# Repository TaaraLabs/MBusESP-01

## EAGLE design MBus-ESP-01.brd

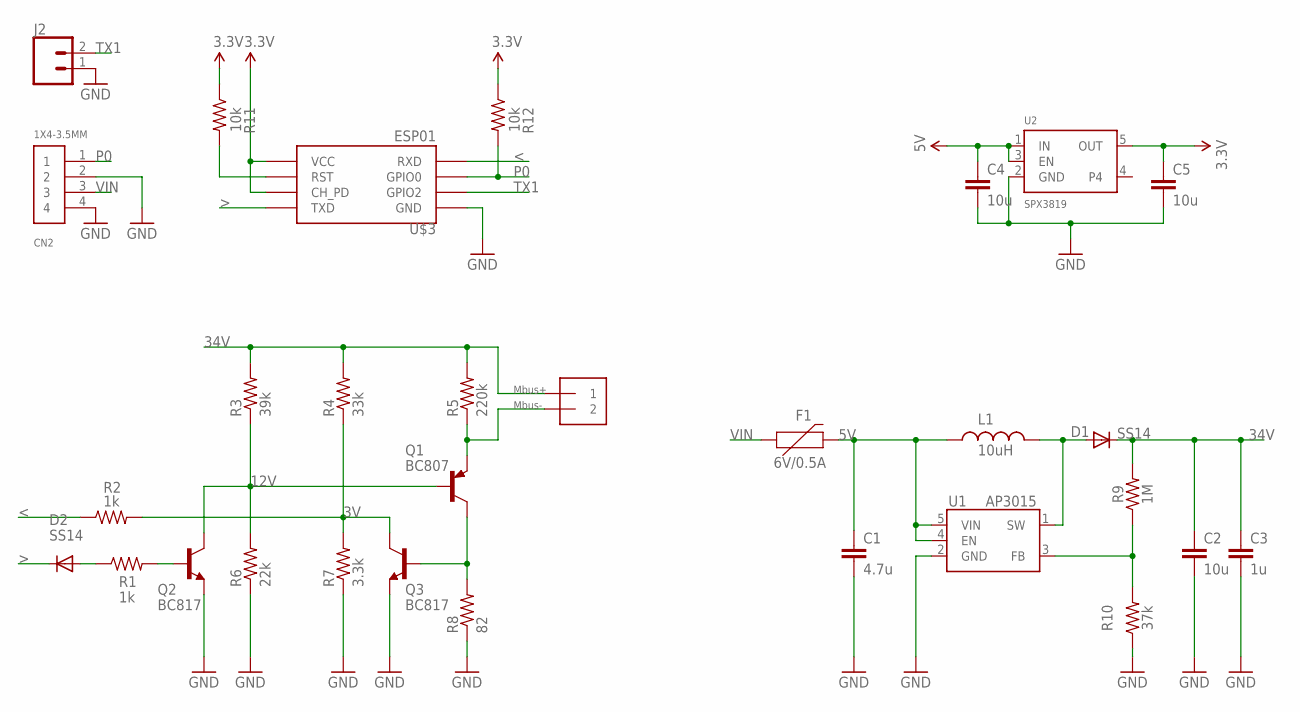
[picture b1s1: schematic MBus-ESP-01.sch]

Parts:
C1: 4.7u; 0805
C2: 10u; 1206
C3: 1u; 1206
C4, C5: 10u; 0603-CAP
CN2: 1X4-3.5MM; 1X04-3.5MM
D1, D2: SS14; SOD-123
F1: 6V/0.5A; 1206
J1: 1X2-3.5MM
J2: CONN_021X02_NO_SILK; 1X02_NO_SILK
L1: 10uH; B82462G
Q1: BC807; SOT23-BEC
Q2, Q3: BC817; SOT23-BEC
R1, R2: 1k; 0805
R3: 39k; 0805
R4: 33k; 0805
R5: 220k; 1206
R6: 22k; 0805
R7: 3.3k; 0805
R8: 82; 1206
R9: 1M; 0805
R10: 37k; 0805
R11, R12: 10k; 0805
U1: AP3015; SOT-23-5
U2: SPX3819; SOT23-5
U$3: ESP01

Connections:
3.3V: C5.1, R11.1, R12.1, U2.5 (OUT), U$3.CH_PD, U$3.VCC
3V: Q3.C, R2.2, R4.1, R7.2
5V: C1.1, C4.1, F1.2, L1.P$1 (1), U1.4 (EN), U1.5 (VIN), U2.1 (IN), U2.3 (EN)
12V: Q1.B, Q2.C, R3.1, R6.2
34V: C2.1, C3.1, D1.C, J1.1, R3.2, R4.2, R5.2, R9.2
<: R2.1, U$3.RX (RXD)
>: D2.C, U$3.TX (TXD)
GND: C1.2, C2.2, C3.2, C4.2, C5.2, CN2.2, CN2.4, J2.1, Q2.E, Q3.E, R6.1, R7.1, R8.1, R10.1, U1.2 (GND), U2.2 (GND), U$3.GND
MBUS-: J1.2, Q1.E, R5.1
unnamed: Q1.C, Q3.B, R8.2
unnamed: R9.1, R10.2, U1.3 (FB)
unnamed: D1.A, L1.P$2 (2), U1.1 (SW)
unnamed: D2.A, R1.1
unnamed: Q2.B, R1.2
P0: CN2.1, R12.2, U$3.GPIO0
RST: R11.2, U$3.RST
TX1: J2.2, U$3.GPIO2
VIN: CN2.3, F1.1

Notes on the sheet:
Mbus+
Mbus-

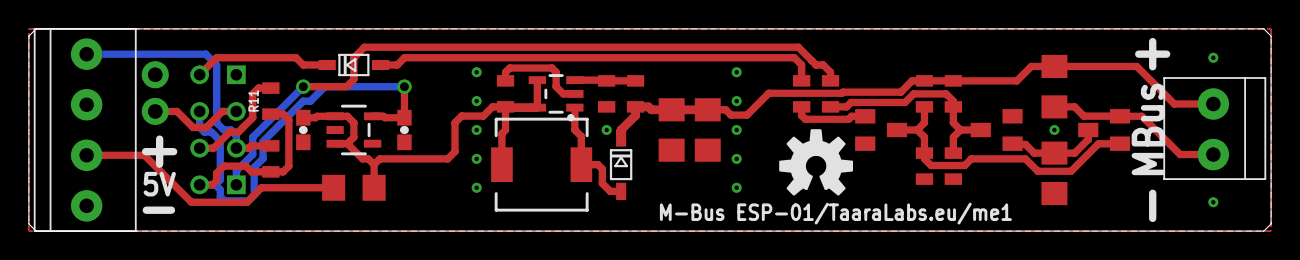
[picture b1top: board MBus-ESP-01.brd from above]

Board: 2 copper layers, 86.0 x 14.0 mm, 32 parts (1 on the bottom side), 18 nets.

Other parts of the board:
U$1, U$2: OSHW-LOGO-M

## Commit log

2019-03-23 Eagle files

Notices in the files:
parts and their libraries:
SparkFun: Licensing: CC v3.0 Share-Alike You are welcome to use this library for commercial purposes.
SparkFun-Capacitors: Licensing: Creative Commons ShareAlike 4.0 International - https://creativecommons.org/licenses/by-sa/4.0
